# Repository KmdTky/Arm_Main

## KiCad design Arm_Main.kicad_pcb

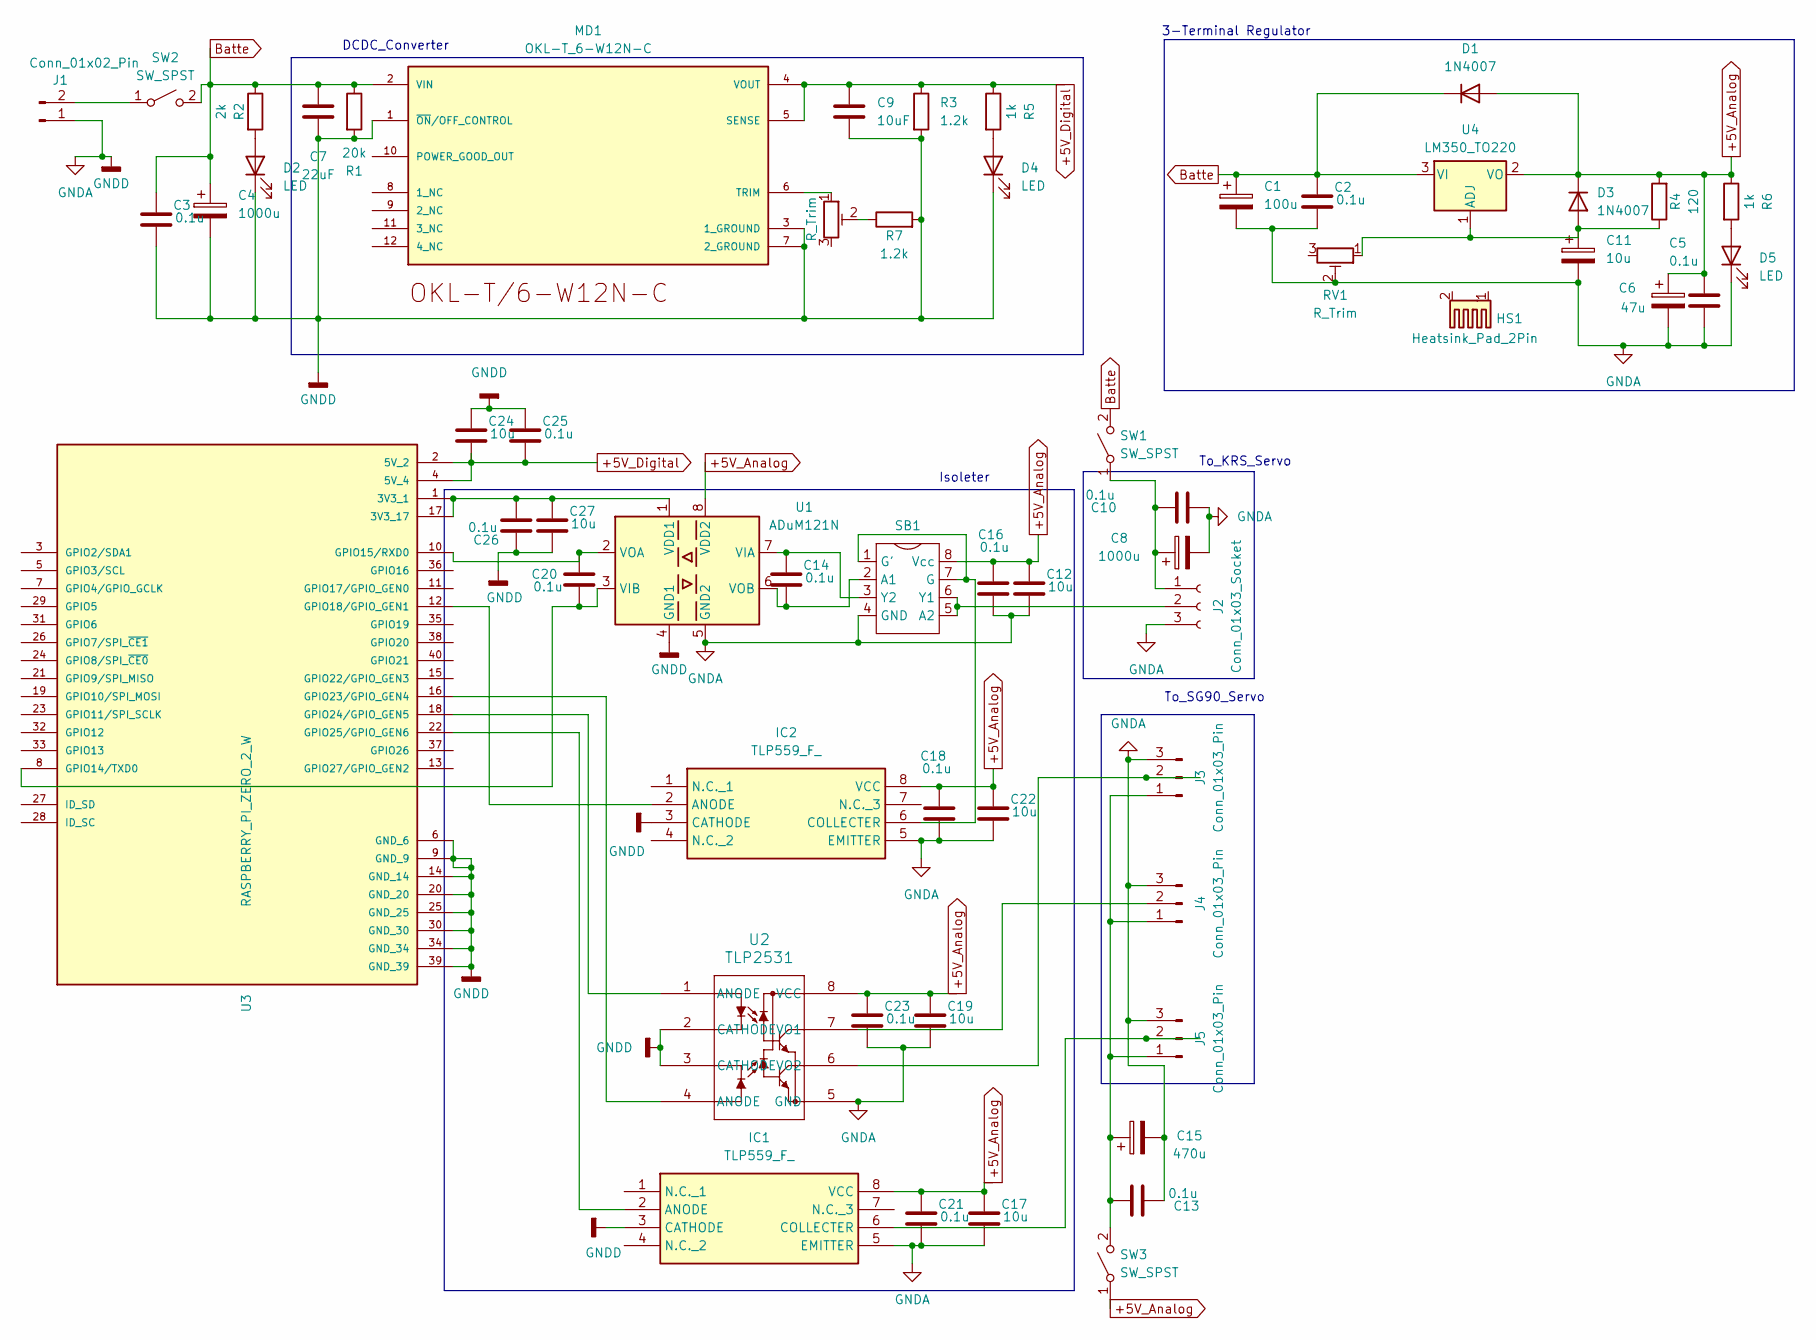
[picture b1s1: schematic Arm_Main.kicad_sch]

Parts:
C1: 100u; CP_Radial_D5.0mm_P2.50mm
C2, C3, C5, C10, C13, C14, C16, C18, C20, C21, C23, C25, C26: 0.1u; C_Disc_D5.1mm_W3.2mm_P5.00mm
C4, C8: 1000u; CP_Radial_D10.0mm_P5.00mm
C6: 47u; CP_Radial_D5.0mm_P2.50mm
C7: 22uF; C_Disc_D5.1mm_W3.2mm_P5.00mm
C9: 10uF; C_Disc_D5.1mm_W3.2mm_P5.00mm
C11: 10u; CP_Radial_D5.0mm_P2.50mm
C12, C17, C19, C22, C24, C27: 10u; C_Disc_D5.1mm_W3.2mm_P5.00mm
C15: 470u; CP_Radial_D5.0mm_P2.50mm
D1, D3: 1N4007; D_A-405_P7.62mm_Horizontal
D2, D4, D5: LED; LED_D3.0mm
HS1: Heatsink_Pad_2Pin; heatsink23.5_17_25mm
IC1, IC2: TLP559_F_; DIP762W60P254L966H485Q8N; Manufacturer_Part_Number TLP559(F)
J1: Conn_01x02_Pin; AMASS_XT30U-F_1x02_P5.0mm_Vertical
J2: Conn_01x03_Socket; JST_XH_B3B-XH-A_1x03_P2.50mm_Vertical
J3, J4, J5: Conn_01x03_Pin; PinHeader_1x03_P2.54mm_Vertical
MD1: OKL-T_6-W12N-C; MURATA_OKL-T-6-W12N-C_0; MOUSER_PART_NUMBER 580-OKL-T/6-W12N-C; MOUSER_DESCRIPTION Non-Isolated DC/DC Converters 12Vin .59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
R1: 20k; R_Axial_DIN0207_L6.3mm_D2.5mm_P10.16mm_Horizontal
R2: 2k; R_Axial_DIN0207_L6.3mm_D2.5mm_P10.16mm_Horizontal
R3, R7: 1.2k; R_Axial_DIN0207_L6.3mm_D2.5mm_P10.16mm_Horizontal
R4: 120; R_Axial_DIN0207_L6.3mm_D2.5mm_P10.16mm_Horizontal
R5, R6: 1k; R_Axial_DIN0207_L6.3mm_D2.5mm_P10.16mm_Horizontal
RV1, RV2: R_Trim; Potentiometer_ACP_CA9-V10_Vertical
SB1: TC7WH241FK
SW1, SW2, SW3: SW_SPST; Hadou_Sw
U1: ADuM121N; SOIC-8_3.9x4.9mm_P1.27mm
U2: TLP2531; U_DIP8_11-10C4S_TOS
U3: RASPBERRY_PI_ZERO_2_W; MODULE_RASPBERRY_PI_ZERO_2_W; PARTREV April 2024
U4: LM350_TO220; TO-220-3_Vertical

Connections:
+5V_Analog: C5.1, C6.1, C12.1, C16.1, C17.1, C18.1, C19.1, C21.1, C22.1, C23.1, D1.2 (A), D3.1 (K), IC1.8 (VCC), IC2.8 (VCC), R4.2, R6.1, SB1.8 (Vcc), SW3.1 (A), U1.8 (VDD2), U2.8 (VCC), U4.2 (VO)
+5V_Digital: C9.1, C24.2, C25.2, MD1.4 (VOUT), MD1.5 (SENSE), R3.1, R5.1, U3.2 (5V_2), U3.4 (5V_4)
Batte: C1.1, C2.1, C3.1, C4.1, C7.1, D1.1 (K), MD1.2 (VIN), R1.1, R2.1, SW1.2 (B), SW2.2 (B), U4.3 (VI)
GNDA: C1.2, C2.2, C3.2, C4.2, C5.2, C6.2, C7.2, C8.2, C9.2, C10.2, C11.2, C12.2, C13.2, C15.2, C16.2, C17.2, C18.2, C19.2, C21.2, C22.2, C23.2, C24.1, C25.1, C26.1, C27.2, D2.1 (K), D4.1 (K), D5.1 (K), IC1.3 (CATHODE), IC1.5 (EMITTER), IC2.3 (CATHODE), IC2.5 (EMITTER), J1.1, J2.3, J3.3, J4.3, J5.3, MD1.1 (~ON/OFF_CONTROL), MD1.3 (1_GROUND), MD1.7 (2_GROUND), R1.2, R3.2, R7.2, RV1.2, SB1.4 (GND), U1.4 (GND1), U1.5 (GND2), U2.2 (CATHODE), U2.3 (CATHODE), U2.5 (GND), U3.6 (GND_6), U3.9 (GND_9), U3.14 (GND_14), U3.20 (GND_20), U3.25 (GND_25), U3.30 (GND_30), U3.34 (GND_34), U3.39 (GND_39)
unnamed: D2.2 (A), R2.2
unnamed: C11.1, D3.2 (A), R4.1, RV1.1, U4.1 (ADJ)
unnamed: D4.2 (A), R5.2
unnamed: D5.2 (A), R6.2
unnamed: IC1.2 (ANODE), U3.22 (GPIO25/GPIO_GEN6)
unnamed: IC1.6 (COLLECTER), J5.2
unnamed: IC2.2 (ANODE), U3.12 (GPIO18/GPIO_GEN1)
unnamed: IC2.6 (COLLECTER), SB1.1 (G'), SB1.7 (G)
unnamed: J1.2, SW2.1 (A)
unnamed: C8.1, C10.1, J2.1, SW1.1 (A)
unnamed: J2.2, SB1.5 (A2), SB1.6 (Y1)
unnamed: C13.1, C15.1, J3.1, J4.1, J5.1, SW3.2 (B)
unnamed: J3.2, U2.6 (VO2)
unnamed: J4.2, U2.7 (VO1)
unnamed: MD1.6 (TRIM), RV2.1
unnamed: R7.1, RV2.2
unnamed: C14.2, SB1.2 (A1), U1.6 (VOB)
unnamed: C14.1, SB1.3 (Y2), U1.7 (VIA)
unnamed: C26.2, C27.1, U1.1 (VDD1), U3.1 (3V3_1), U3.17 (3V3_17)
unnamed: C20.2, U1.3 (VIB), U3.8 (GPIO14/TXD0)
unnamed: C20.1, U1.2 (VOA), U3.10 (GPIO15/RXD0)
unnamed: U2.4 (ANODE), U3.16 (GPIO23/GPIO_GEN4)
unnamed: U2.1 (ANODE), U3.18 (GPIO24/GPIO_GEN5)

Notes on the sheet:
To_SG90_Servo
3-Terminal Regulator
To_KRS_Servo
Isoleter
DCDC_Converter

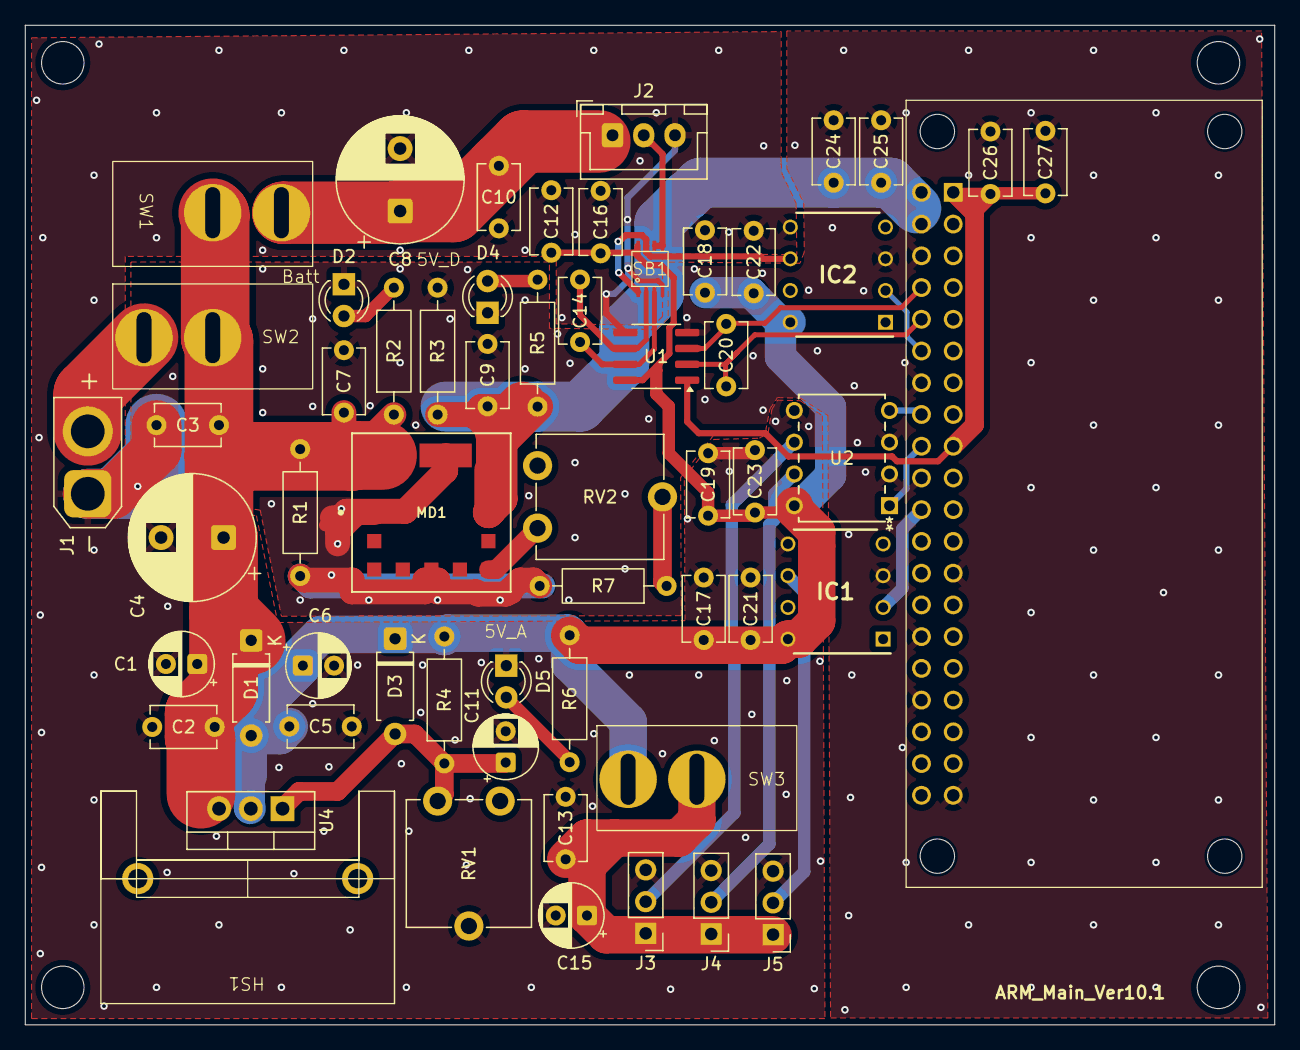
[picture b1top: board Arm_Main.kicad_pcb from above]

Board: 2 copper layers, 100.0 x 80.0 mm, 58 parts (1 on the bottom side), 27 nets.

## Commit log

2025-09-05 ver5
2025-09-05 parts
2025-09-07 25/9/7
2025-09-07 25/9/7-2
2025-09-07 25/9/7-3
2025-09-08 ver6
2025-09-08 Gerber
2025-09-08 parts_ver6
2025-09-08 parts_ver6.1
2025-09-09 Ver_7
2025-09-26 ver.8.pre
2025-09-27 v8.1
2025-09-27 ver8.1 parts
2025-09-29 ver9
2025-09-29 ver9_add3dmodel
2025-10-01 ver10
2025-10-01 ver10_partslists
2025-10-02 ver10.1
